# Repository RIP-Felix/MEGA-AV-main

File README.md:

# MegaAV
Sega Genesis audio and video bypass, incorporating an entirely new audio circuit design that restores mono audio, along with native composite and S-video generation.

Attribution: Credit where Credit's due

Timeline of events:
ACE9921 & Villahed94 developed the original Mega Amp 1.0. Inception for a mod board that combines the Mega Amp with an RGB video amplifier was Bob from RetroRGB's idea. Rene from db Electronics designed the first build. Tienfeng designed the second with a modified version of the then new Mega Amp 2.0, on which Jose Cruz helped with testing. That became the Triple Bypass v2.

Zaxour forked the 3BPv2 to support Composite restore with the 3BPV2+ and is continuing development of a Quadruple Bypass that will support S-video.

For most of the 6 years between the Mega Amp 2.0 and 3.0, Ace was pretty much developing alone. Villahed94, eep386, and ACE9921 were throwing ideas around, but nobody except Ace was doing anything. I want to make it clear that the Mega Amp 3 is it's own standalone thing still in development and that the Mega Audio is NOT to be confused with it. Ace is not associated with the MegaAV.

While they may use similar circuit topology, their goals are different, and they must not be used interchangeably

RIP-Felix incepted the idea of restoring Mono Audio for RF compatibility. RGBeter incepted the idea of recreating Composite video using a modern encoder, taking the opportunity to fix the luma trap. At that point it was still a derivative work of the 3BPV2+. Villahed94 agreed to join the MegaAV team to finish and implement the Mega Audio for both inboard and MegaAV mod board installations. The three of us tested and refined finalized values, and implemented the designs together. Both RIP-Felix and RGBeter designed the MegaAV PCB. The only part of the circuit that has remained unchanged is the THS7374 RGB amplifier. 

So the Mega AV is actually 2 mods in one. The Mega Video developed by RIP-Felix, RGBeter, and Villahed94. Mega Audio was developed with help from Villahed94 and others along the way. Villahed94, RGBeter and RIP-Felix dialed in PSG and FM resistor values to dial in MD fourier. That said I (RIP-Felix) want to thank and credit everyone involved in these mods regardless of how much of their contributions made it into the current version of Mega AV. It's been a collective effort and everyone should be credited for the hard work they've put in! Massive thanks to all of you!
 
NOTEs:
- Fujitsu ASICs, 315-5708-01 and 315-5660-01 needed an additional pulldown resistor. Instead of bridging jumper C, solder a 200Ohm 1% or lower tolerance resistor to it. May apply to Model 1 VA7 through Model 2 VA1.8. The Suffix -01 indicates it's a Fujitsu Chip. This DOES NOT apply to chips LACKING the suffix "-01".
- Adds a ZIF connector for a future ribbon cable design to greatly simplify installation

(instructions pending, same as 3bp install except composite and mono must also be isolated from the din, and the subcarrier line must be routed to the MegaAV)
### When routing the subcarrier line, make sure it's a shielded coaxial cable or twisted pair to prevent jailbars

Instructions pending:
## Model 1 Installation Guides
[Model 1 - VA1-VA6]
[Model 1 - VA7]
## Model 2 Installation Guides
[Model 2 - VA0-1.8]
[Model 2 - VA2]
[Model 2 - VA2.3] (needed)
[Model 2 - VA3]
[Model 2 - VA4]

## Model 3 Installation Guides
[Model 3 - VA1] (needed)
[Model 3 - VA2] (needed)

## Sega CDX
[CDX]

## Other
[Other forms of Genesis]

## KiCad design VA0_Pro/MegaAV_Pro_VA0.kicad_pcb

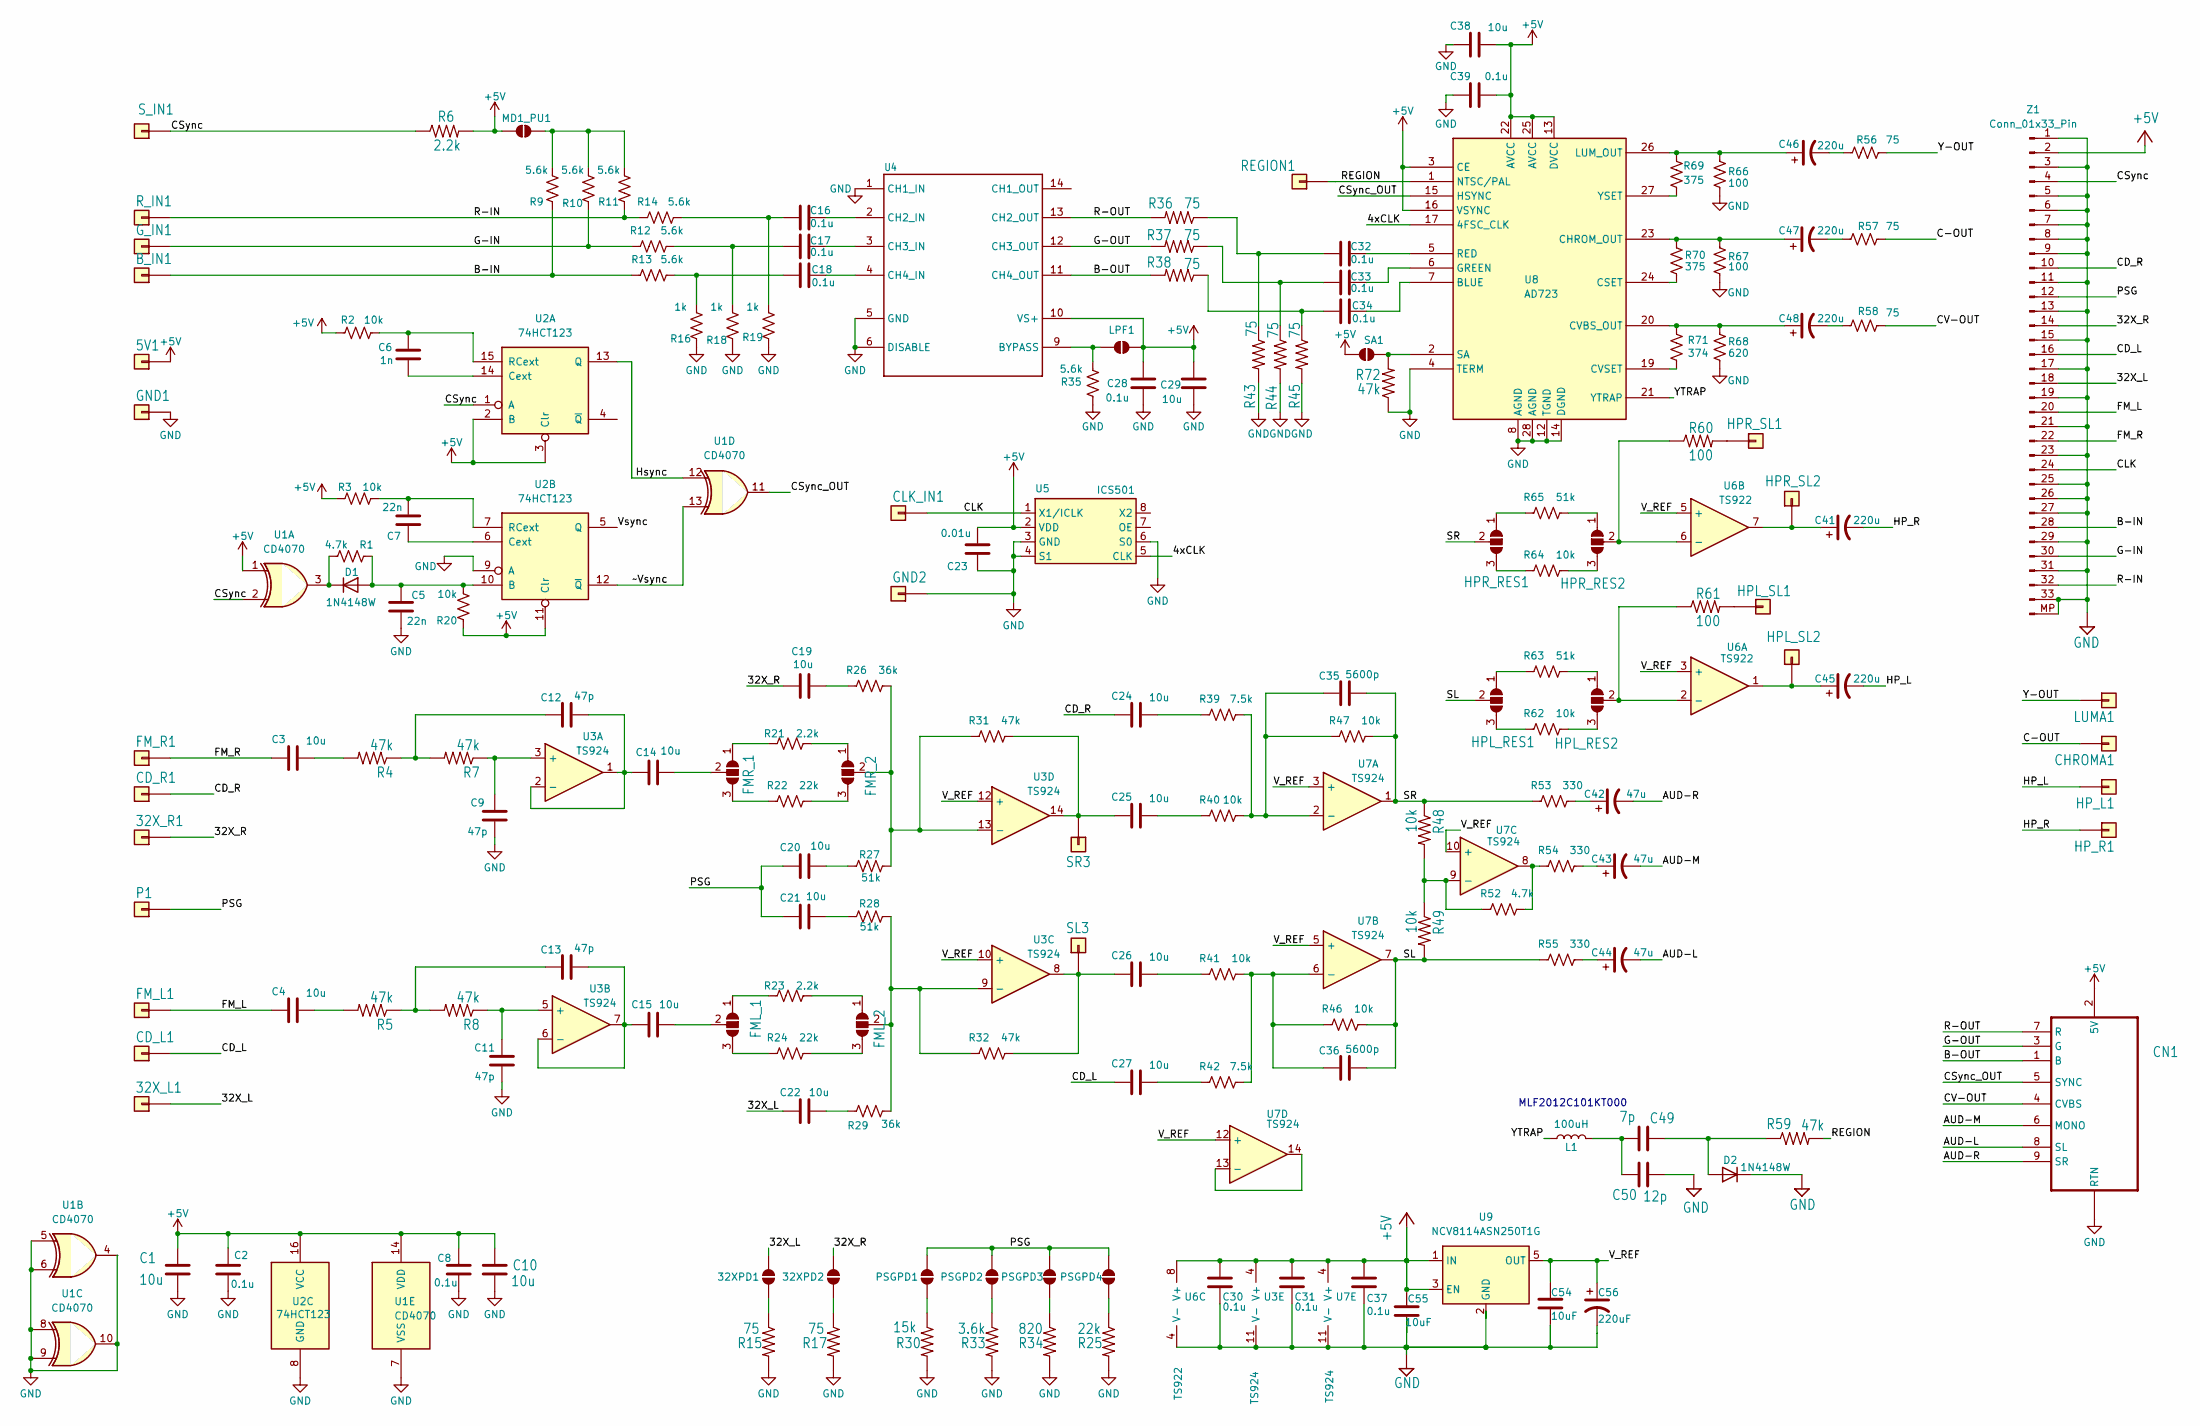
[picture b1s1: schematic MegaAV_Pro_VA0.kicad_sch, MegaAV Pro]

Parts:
5V1: SolderWirePad_1x01_SMD_1x2mm
32XPD1, 32XPD2: SolderJumper-2_P1.3mm_Open_RoundedPad1.0x1.5mm
32X_L1, 32X_R1: SMD_Conn_01x01; SolderWirePad_1x01_SMD_1x2mm
B_IN1: SolderWirePad_1x01_SMD_1x2mm
C1, C3, C4, C10, C14, C15, C19, C20, C21, C22, C24, C25, C26, C27, C29, C38: 10u; C_0805_2012Metric
C2, C8, C16, C17, C18, C30, C31, C32, C33, C34, C37, C39: 0.1u; C_0402_1005Metric
C5, C7: 22n; C_0402_1005Metric
C6: 1n; C_0402_1005Metric
C9, C11, C12, C13: 47p; C_0402_1005Metric
C23: 0.01u; C_0402_1005Metric
C28: 0.1u; C_0805_2012Metric
C35, C36: 5600p; C_0402_1005Metric
C41, C45, C46, C47, C48: 220u; CP_EIA-3528-15_AVX-H
C42, C43, C44: 47u; C_1206_3216Metric
C49: 7p; C_0402_1005Metric
C50: 12p; C_0402_1005Metric
C54: 10uF; C_0805_2012Metric; MPN VJ0805A330FXJPW1BC; LCSC Part # C520060
C55: 10uF; C_0805_2012Metric
C56: 220uF; CP_EIA-3528-15_AVX-H
CD_L1: SMD_Conn_01x01; SolderWirePad_1x01_SMD_1x2mm
CD_R1: SMD_Conn_01x01; SolderWirePad_1x01_SMD_1x2mm
CHROMA1: SMD_Conn_01x01; SolderWirePad_1x01_SMD_1x2mm
CLK_IN1: SolderWirePad_1x01_SMD_1x2mm
CN1: MD-90SM_MD2; MD90SM-MD2
D1, D2: 1N4148W; D_SOD-323F
FML_1, FML_2: SolderJumper_3_Open; SolderJumper-3_P1.3mm_Open_RoundedPad1.0x1.5mm
FMR_1, FMR_2: SolderJumper_3_Open; SolderJumper-3_P1.3mm_Open_RoundedPad1.0x1.5mm
FM_L1: SMD_Conn_01x01; SolderWirePad_1x01_SMD_1x2mm
FM_R1: SMD_Conn_01x01; SolderWirePad_1x01_SMD_1x2mm
GND1: SolderWirePad_1x01_SMD_1x2mm
GND2: SMD_Conn_01x01; SolderWirePad_1x01_SMD_1x2mm
G_IN1: SolderWirePad_1x01_SMD_1x2mm
HPL_RES1, HPL_RES2: SolderJumper_3_Open; SolderJumper-3_P1.3mm_Open_RoundedPad1.0x1.5mm
HPL_SL1, HPL_SL2: SMD_Conn_01x01; SolderWirePad_1x01_SMD_1x2mm
HPR_RES1, HPR_RES2: SolderJumper_3_Open; SolderJumper-3_P1.3mm_Open_RoundedPad1.0x1.5mm
HPR_SL1, HPR_SL2: SMD_Conn_01x01; SolderWirePad_1x01_SMD_1x2mm
HP_L1: SMD_Conn_01x01; SolderWirePad_1x01_SMD_1x2mm
HP_R1: SMD_Conn_01x01; SolderWirePad_1x01_SMD_1x2mm
L1: 100uH; L_0805_2012Metric
LPF1: SolderJumper-2_P1.3mm_Open_RoundedPad1.0x1.5mm
LUMA1: SMD_Conn_01x01; SolderWirePad_1x01_SMD_1x2mm
MD1_PU1: SolderJumper-2_P1.3mm_Open_RoundedPad1.0x1.5mm
P1: SMD_Conn_01x01; SolderWirePad_1x01_SMD_1x2mm
PSGPD1, PSGPD2, PSGPD3, PSGPD4: SolderJumper-2_P1.3mm_Open_RoundedPad1.0x1.5mm
R1, R52: 4.7k; R_0402_1005Metric
R2, R3, R20, R40, R41, R46, R47, R48, R49, R62, R64: 10k; R_0402_1005Metric
R4, R5, R7, R8, R31, R32, R59, R72: 47k; R_0402_1005Metric
R6, R21, R23: 2.2k; R_0402_1005Metric
R9, R10, R11, R12, R13, R14, R35: 5.6k; R_0603_1608Metric
R15, R17, R36, R37, R38, R43, R44, R45, R56, R57, R58: 75; R_0603_1608Metric
R16, R18, R19: 1k; R_0402_1005Metric
R22, R24, R25: 22k; R_0402_1005Metric
R26, R29: 36k; R_0603_1608Metric
R27, R28, R63, R65: 51k; R_0402_1005Metric
R30: 15k; R_0402_1005Metric
R33: 3.6k; R_0603_1608Metric
R34: 820; R_0603_1608Metric
R39, R42: 7.5k; R_0603_1608Metric
R53, R54, R55: 330; R_0402_1005Metric
R60, R61, R66, R67: 100; R_0402_1005Metric
R68: 620; R_0402_1005Metric
R69, R70: 375; R_0402_1005Metric
R71: 374; R_0402_1005Metric
REGION1: SolderWirePad_1x01_SMD_1x2mm
R_IN1: SolderWirePad_1x01_SMD_1x2mm
SA1: SolderJumper-2_P1.3mm_Open_RoundedPad1.0x1.5mm
SL3: SMD_Conn_01x01; SolderWirePad_1x01_SMD_1x2mm
SR3: SMD_Conn_01x01; SolderWirePad_1x01_SMD_1x2mm
S_IN1: SolderWirePad_1x01_SMD_1x2mm
U1: CD4070; TSSOP-14_4.4x5mm_P0.65mm
U2: 74HCT123; TSSOP-16_4.4x5mm_P0.65mm
U3, U7: TS924; TSSOP-14_4.4x5mm_P0.65mm
U4: THS7374; TSSOP-14_4.4x5mm_P0.65mm
U5: ICS501; SOIC-8_3.9x4.9mm_P1.27mm
U6: TS922; SO-8_3.9x4.9mm_P1.27mm
U8: AD723; TSSOP-28_6.1x9.7mm_P0.65mm
U9: NCV8114ASN250T1G; TSOT-23-5
Z1: Conn_01x33_Pin; Molex_502244-3330_1x33-1MP_P0.5mm_Horizontal

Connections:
+5V: 5V1.1, C1.1, C2.1, C8.1, C10.1, C23.2, C28.1, C29.1, C30.1, C31.1, C37.1, C38.2, C39.2, C55.1, CN1.2 (5V), LPF1.2 (B), MD1_PU1.2 (B), R2.2, R3.1, R6.2, R20.1, SA1.1 (A), U1.1, U1.14 (VDD), U2.2 (B), U2.3 (Clr), U2.11 (Clr), U2.16 (VCC), U3.4 (V+), U4.10 (VS+), U5.2 (VDD), U6.8 (V+), U7.4 (V+), U8.3 (CE), U8.13 (DVCC), U8.16 (VSYNC), U8.22 (AVCC), U8.25 (AVCC), U9.1 (IN), U9.3 (EN), Z1.2
/4xCLK: U5.5 (CLK), U8.17 (4FSC_CLK)
/32X_L: 32XPD1.2 (B), 32X_L1.1, C22.1, Z1.18
/32X_R: 32XPD2.2 (B), 32X_R1.1, C19.1, Z1.14
/AUD-L: C44.2, CN1.8 (SL)
/AUD-M: C43.2, CN1.6 (MONO)
/AUD-R: C42.2, CN1.9 (SR)
/B-IN: B_IN1.1, R9.1, R13.1, Z1.28
/B-OUT: CN1.1 (B), R38.2, U4.11 (CH4_OUT)
/C-OUT: CHROMA1.1, R57.2
/CD_L: C27.1, CD_L1.1, Z1.16
/CD_R: C24.1, CD_R1.1, Z1.10
/CLK: CLK_IN1.1, U5.1 (X1/ICLK), Z1.24
/CSync: R6.1, S_IN1.1, U1.2, U2.1 (A), Z1.4
/CSync_OUT: CN1.5 (SYNC), U1.11, U8.15 (HSYNC)
/CV-OUT: CN1.4 (CVBS), R58.2
/FM_L: C4.1, FM_L1.1, Z1.20
/FM_R: C3.1, FM_R1.1, Z1.22
/G-IN: G_IN1.1, R10.1, R12.1, Z1.30
/G-OUT: CN1.3 (G), R37.2, U4.12 (CH3_OUT)
/HP_L: C45.2, HP_L1.1
/HP_R: C41.2, HP_R1.1
/Hsync: U1.12, U2.13 (Q)
/PSG: C20.1, C21.1, P1.1, PSGPD1.2 (B), PSGPD2.2 (B), PSGPD3.2 (B), PSGPD4.2 (B), Z1.12
/R-IN: R11.1, R14.1, R_IN1.1, Z1.32
/R-OUT: CN1.7 (R), R36.2, U4.13 (CH2_OUT)
/REGION: R59.2, REGION1.1, U8.1 (NTSC/PAL); also elsewhere on the board
/SL: C36.2, HPL_RES1.2 (C), R46.2, R49.2, R55.1, U7.7
/SR: C35.2, HPR_RES1.2 (C), R47.2, R48.1, R53.1, U7.1
/V_REF: C54.1, C56.1, U3.10 (+), U3.12 (+), U6.3 (+), U6.5 (+), U7.3 (+), U7.5 (+), U7.10 (+), U7.12 (+), U9.5 (OUT)
/Vsync: U2.5 (Q)
/Y-OUT: LUMA1.1, R56.2
/YTRAP: L1.1, U8.21 (YTRAP)
/~Vsync: U1.13, U2.12 (~Q)
GND: C1.2, C2.2, C5.1, C8.2, C9.2, C10.2, C11.2, C23.1, C28.2, C29.2, C30.2, C31.2, C37.2, C38.1, C39.1, C50.2, C54.2, C55.2, C56.2, CN1.S1 (RTN), CN1.S2 (RTN), CN1.S3 (RTN), D2.1 (K), GND1.1, GND2.1, R15.2, R16.1, R17.2, R18.1, R19.1, R25.2, R30.2, R33.2, R34.2, R35.1, R43.2, R44.2, R45.2, R66.2, R67.2, R68.2, R72.1, U1.4, U1.5, U1.6, U1.7 (VSS), U1.8, U1.9, U1.10, U2.8 (GND), U2.9 (A), U3.11 (V-), U4.1 (CH1_IN), U4.5 (GND), U4.6 (DISABLE), U5.3 (GND), U5.4 (S1), U5.6 (S0), U6.4 (V-), U7.11 (V-), U8.4 (TERM), U8.8 (AGND), U8.12 (TGND), U8.14 (DGND), U8.28 (AGND), U9.2 (GND), Z1.1, Z1.3, Z1.5, Z1.6, Z1.7, Z1.8, Z1.9, Z1.11, Z1.13, Z1.15, Z1.17, Z1.19, Z1.21, Z1.23, Z1.25, Z1.26, Z1.27, Z1.29, Z1.31, Z1.33, Z1.MP
unnamed: 32XPD1.1 (A), R15.1
unnamed: 32XPD2.1 (A), R17.1
unnamed: C3.2, R4.2
unnamed: C4.2, R5.2
unnamed: C12.1, R4.1, R7.2
unnamed: C13.1, R5.1, R8.2
unnamed: C16.1, R14.2, R19.2
unnamed: C17.1, R12.2, R18.2
unnamed: C18.1, R13.2, R16.2
unnamed: C19.2, R26.1
unnamed: C20.2, R27.1
unnamed: C21.2, R28.1
unnamed: C22.2, R29.1
unnamed: C24.2, R39.1
unnamed: C25.2, R40.1
unnamed: C26.2, R41.1
unnamed: C27.2, R42.1
unnamed: C32.1, R36.1, R43.1
unnamed: C33.1, R37.1, R44.1
unnamed: C34.1, R38.1, R45.1
unnamed: C42.1, R53.2
unnamed: C43.1, R54.2
unnamed: C44.1, R55.2
unnamed: C46.2, R56.1
unnamed: C47.2, R57.1
unnamed: C48.2, R58.1
unnamed: C49.2, C50.1, L1.2
unnamed: C5.2, D1.2 (A), R1.1, R20.2, U2.10 (B)
unnamed: D1.1 (K), R1.2, U1.3
unnamed: C49.1, D2.2 (A), R59.1
unnamed: FML_1.1 (A), R23.1
unnamed: FML_1.3 (B), R24.1
unnamed: C15.2, FML_1.2 (C)
unnamed: FML_2.1 (A), R23.2
unnamed: FML_2.3 (B), R24.2
unnamed: FML_2.2 (C), R28.2, R29.2, R32.1, U3.9 (-)
unnamed: FMR_1.1 (A), R21.1
unnamed: FMR_1.3 (B), R22.1
unnamed: C14.2, FMR_1.2 (C)
unnamed: FMR_2.1 (A), R21.2
unnamed: FMR_2.3 (B), R22.2
unnamed: FMR_2.2 (C), R26.2, R27.2, R31.1, U3.13 (-)
unnamed: HPL_RES1.1 (A), R63.1
unnamed: HPL_RES1.3 (B), R62.1
unnamed: HPL_RES2.1 (A), R63.2
unnamed: HPL_RES2.3 (B), R62.2
unnamed: HPL_RES2.2 (C), R61.1, U6.2 (-)
unnamed: HPL_SL1.1, R61.2
unnamed: C45.1, HPL_SL2.1, U6.1
unnamed: HPR_RES1.1 (A), R65.1
unnamed: HPR_RES1.3 (B), R64.1
unnamed: HPR_RES2.1 (A), R65.2
unnamed: HPR_RES2.3 (B), R64.2
unnamed: HPR_RES2.2 (C), R60.1, U6.6 (-)
unnamed: HPR_SL1.1, R60.2
unnamed: C41.1, HPR_SL2.1, U6.7
unnamed: LPF1.1 (A), R35.2, U4.9 (BYPASS)
unnamed: MD1_PU1.1 (A), R9.2, R10.2, R11.2
unnamed: PSGPD1.1 (A), R30.1
unnamed: PSGPD2.1 (A), R33.1
unnamed: PSGPD3.1 (A), R34.1
unnamed: PSGPD4.1 (A), R25.1
unnamed: R52.2, R54.1, U7.8
unnamed: R72.2, SA1.2 (B), U8.2 (SA)
unnamed: C26.1, R32.2, SL3.1, U3.8
unnamed: C25.1, R31.2, SR3.1, U3.14
unnamed: C6.1, U2.14 (Cext)
unnamed: C6.2, R2.1, U2.15 (RCext)
unnamed: C7.1, U2.6 (Cext)
unnamed: C7.2, R3.2, U2.7 (RCext)
unnamed: C9.1, R7.1, U3.3 (+)
unnamed: C12.2, C14.1, U3.1, U3.2 (-)
unnamed: C11.1, R8.1, U3.5 (+)
unnamed: C13.2, C15.1, U3.6 (-), U3.7
unnamed: C16.2, U4.2 (CH2_IN)
unnamed: C17.2, U4.3 (CH3_IN)
unnamed: C18.2, U4.4 (CH4_IN)
unnamed: C35.1, R39.2, R40.2, R47.1, U7.2 (-)
unnamed: C36.1, R41.2, R42.2, R46.1, U7.6 (-)
unnamed: R48.2, R49.1, R52.1, U7.9 (-)
unnamed: U7.13 (-), U7.14
unnamed: C34.2, U8.7 (BLUE)
unnamed: C47.1, R67.1, R70.2, U8.23 (CHROM_OUT)
unnamed: R70.1, U8.24 (CSET)
unnamed: C48.1, R68.1, R71.2, U8.20 (CVBS_OUT)
unnamed: R71.1, U8.19 (CVSET)
unnamed: C33.2, U8.6 (GREEN)
unnamed: C46.1, R66.1, R69.1, U8.26 (LUM_OUT)
unnamed: C32.2, U8.5 (RED)
unnamed: R69.2, U8.27 (YSET)

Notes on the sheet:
MLF2012C101KT000

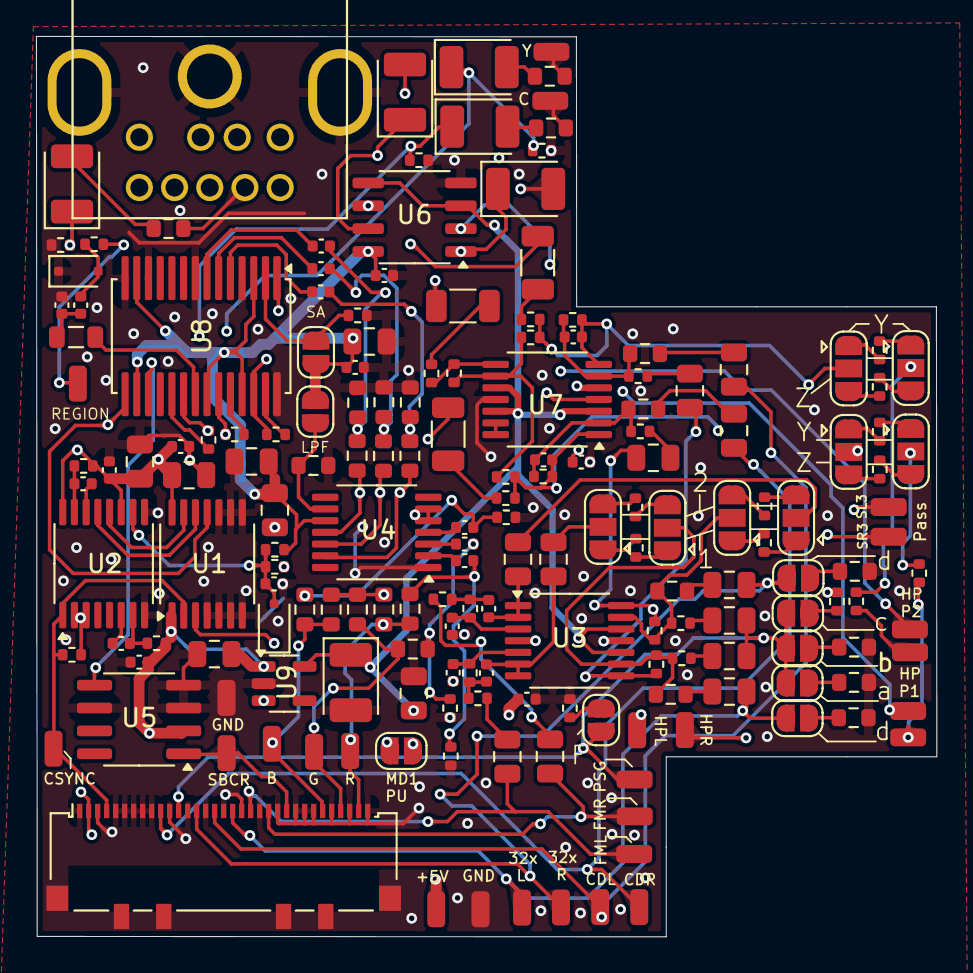
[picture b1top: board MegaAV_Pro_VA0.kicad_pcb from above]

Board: 4 copper layers, 50.0 x 50.0 mm, 179 parts (0 on the bottom side), 124 nets.

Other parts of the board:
REGION: SolderWirePad_1x01_SMD_1x2mm

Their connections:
/REGION: REGION.1; also elsewhere on the board

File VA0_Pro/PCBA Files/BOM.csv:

Designator,Comment,Footprint,LCSC Part #
"R15,R17,R36,R37,R38,R43,R44,R45,R56,R57,R58",75,Resistor_SMD:R_0603_1608Metric,C4275
"R60,R61,R66,R67",100,Resistor_SMD:R_0402_1005Metric,C25076
"R53,R54,R55",330,Resistor_SMD:R_0402_1005Metric,C25104
"R69,R70,R71",374,Resistor_SMD:R_0402_1005Metric,C270604
R68,620,Resistor_SMD:R_0402_1005Metric,C4961
R34,820,Resistor_SMD:R_0603_1608Metric,C23253
C23,0.01u,Capacitor_SMD:C_0402_1005Metric,C15195
"C2,C8,C28,C30,C31,C32,C33,C34,C37,C39",100n,Capacitor_SMD:C_0402_1005Metric,C28233
"C16,C17,C18",0.1u,Capacitor_SMD:C_0402_1005Metric,C1525
L1,100uH,Inductor_SMD:L_0805_2012Metric,C68035
"R2,R3,R20,R40,R41,R46,R47,R48,R49,R62,R64",10k,Resistor_SMD:R_0402_1005Metric,C25744
"C1,C3,C4,C10,C14,C15,C19,C20,C21,C22,C24,C25,C26,C27,C29,C38,C54,C55",10u,Capacitor_SMD:C_0805_2012Metric,C15850
C50,12p,Capacitor_SMD:C_0402_1005Metric,C1547
R30,15k,Resistor_SMD:R_0402_1005Metric,C25756
"R16,R18,R19",1k,Resistor_SMD:R_0402_1005Metric,C11702
C6,1n,Capacitor_SMD:C_0402_1005Metric,C1523
"D1,D2",1N4148W,Diode_SMD:D_SOD-323,C2128
"R6,R21,R23",2.2k,Resistor_SMD:R_0402_1005Metric,C25879
"C41,C45,C46,C47,C48,C56",220u,Capacitor_Tantalum_SMD:CP_EIA-3528-15_AVX-H,C122649
"R22,R24,R25",22k,Resistor_SMD:R_0402_1005Metric,C25768
"C5,C7",22n,Capacitor_SMD:C_0402_1005Metric,C1532
R33,3.6k,Resistor_SMD:R_0603_1608Metric,C22980
"R26,R29",36k,Resistor_SMD:R_0603_1608Metric,C23147
"R1,R52",4.7k,Resistor_SMD:R_0402_1005Metric,C25900
"R4,R5,R7,R8,R31,R32,R59,R72",47k,Resistor_SMD:R_0402_1005Metric,C25792
"C9,C11,C12,C13",47p,Capacitor_SMD:C_0402_1005Metric,C1567
"C42,C43,C44",47u,Capacitor_SMD:C_1206_3216Metric,C96123
"R9,R10,R11,R12,R13,R14,R35",5.6k,Resistor_SMD:R_0603_1608Metric,C23189
"R27,R28,R63,R65",51k,Resistor_SMD:R_0402_1005Metric,C25794
"C35,C36",5600p,Capacitor_SMD:C_0402_1005Metric,C2976066
"R39,R42",7.5k,Resistor_SMD:R_0603_1608Metric,C23234
U2,74HCT123,Package_SO:TSSOP-16_4.4x5mm_P0.65mm,C191980
C49,7p,Capacitor_SMD:C_0402_1005Metric,C5448838
U8,AD723,Package_SO:TSSOP-28_6.1x9.7mm_P0.65mm,
U1,CD4070,Package_SO:TSSOP-14_4.4x5mm_P0.65mm,C2865674
Z1,Conn_01x33_Pin,Connector_FFC-FPC:Molex_502244-3330_1x33-1MP_P0.5mm_Horizontal,
U5,ICS501,Package_SO:SOIC-8_3.9x4.9mm_P1.27mm,
CN1,MD-90SM_MD2,MyLibrary:MD90SM-MD2,
U9,2.5v linear Regulator,Package_TO_SOT_SMD:TSOT-23-5,C22466441
U4,THS7374,Package_SO:TSSOP-14_4.4x5mm_P0.65mm,
U6,TS922,Package_SO:TSSOP-8_4.4x3mm_P0.65mm,C93687
"U3,U7",TS924,Package_SO:TSSOP-14_4.4x5mm_P0.65mm,

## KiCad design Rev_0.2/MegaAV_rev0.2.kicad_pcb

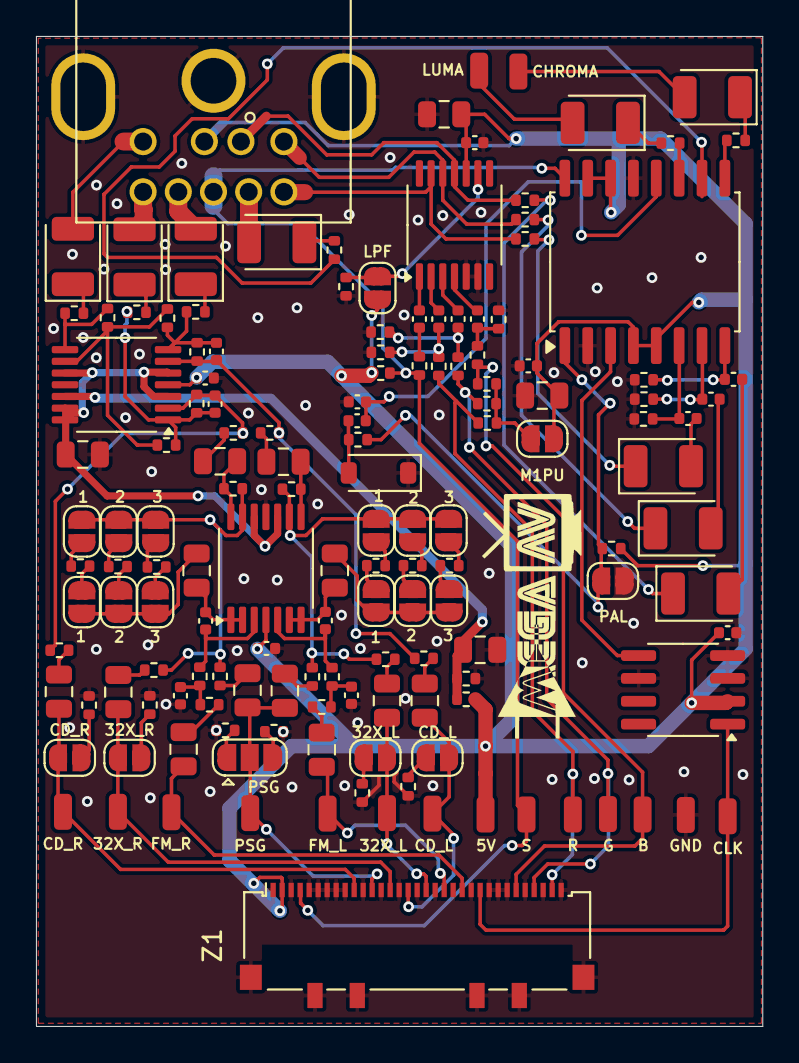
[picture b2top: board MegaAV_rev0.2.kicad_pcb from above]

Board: 2 copper layers, 40.4 x 55.0 mm, 148 parts (0 on the bottom side), 103 nets.

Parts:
5V: SolderWirePad_1x01_SMD_1x2mm
32X_L, 32X_R: SMD_Conn_01x01; SolderWirePad_1x01_SMD_1x2mm
32X_L#2, 32X_R#2: SolderJumper-2_P1.3mm_Open_RoundedPad1.0x1.5mm
B: SolderWirePad_1x01_SMD_1x2mm
C1: 0.01u; C_0402_1005Metric
C2, C3, C8, C9, C14, C15, C16, C17, C19, C20, C21, C22, C23, C32, C42, C45: 10u; C_0805_2012Metric
C4, C5, C6, C7: 27p; C_0402_1005Metric
C10, C11, C12, C13, C18, C27, C28, C29, C33, C43, C44: 0.1u; C_0402_1005Metric
C24, C25, C26, C39, C40, C41: 220u; CP_EIA-3528-15_AVX-H
C30, C31: 5600p; C_0402_1005Metric
C34, C35, C36: 47u; CP_EIA-3528-15_AVX-H
C37: 9p; C_0402_1005Metric
C38: 18p; C_0402_1005Metric
CD_L: SMD_Conn_01x01; SolderWirePad_1x01_SMD_1x2mm
CD_L#2: SolderJumper-2_P1.3mm_Open_RoundedPad1.0x1.5mm
CD_R: SolderJumper-2_P1.3mm_Open_RoundedPad1.0x1.5mm
CD_R#2: SMD_Conn_01x01; SolderWirePad_1x01_SMD_1x2mm
CHROMA: SMD_Conn_01x01; SolderWirePad_1x01_SMD_1x2mm
CLK: SolderWirePad_1x01_SMD_1x2mm
CN1: MD-90SM_MD2; MD90SM-MD2
D1: 1N4148W; D_SOD-123
FM_L: SMD_Conn_01x01; SolderWirePad_1x01_SMD_1x2mm
FM_L1-1, FM_L1-2, FM_L2-1, FM_L2-2, FM_L3-1, FM_L3-2: SolderJumper_2_Open; SolderJumper-2_P1.3mm_Open_RoundedPad1.0x1.5mm
FM_R: SMD_Conn_01x01; SolderWirePad_1x01_SMD_1x2mm
FM_R1-1, FM_R1-2, FM_R2-1, FM_R2-2, FM_R3-1, FM_R3-2: SolderJumper_2_Open; SolderJumper-2_P1.3mm_Open_RoundedPad1.0x1.5mm
G: SolderWirePad_1x01_SMD_1x2mm
GND: SolderWirePad_1x01_SMD_1x2mm
LPF: SolderJumper-2_P1.3mm_Open_RoundedPad1.0x1.5mm
LUMA: SMD_Conn_01x01; SolderWirePad_1x01_SMD_1x2mm
M1PU: SolderJumper-2_P1.3mm_Open_RoundedPad1.0x1.5mm
PAL: SolderJumper-2_P1.3mm_Open_RoundedPad1.0x1.5mm
PSG: SMD_Conn_01x01; SolderWirePad_1x01_SMD_1x2mm
PSG#2: SolderJumper_3_Open; SolderJumper-3_P1.3mm_Open_RoundedPad1.0x1.5mm
R: SolderWirePad_1x01_SMD_1x2mm
R1, R2, R3, R4, R20, R23, R48, R49: 100k; R_0402_1005Metric
R5, R8: 2.2k; R_0402_1005Metric
R6, R9, R10, R11, R12, R13, R16, R32, R42: 5.62k; R_0402_1005Metric
R7: 750; R_0402_1005Metric
R14, R15, R17: 1k; R_0402_1005Metric
R18, R25, R33, R34, R35, R36, R37, R43, R44, R46, R54, R55, R56: 75; R_0402_1005Metric
R19, R22, R58, R59: 10k; R_0402_1005Metric
R21, R24: 130k; R_0402_1005Metric
R26, R27, R28, R29: 210k; R_0402_1005Metric
R30, R31: 300k; R_0402_1005Metric
R38, R41: 21k; R_0402_1005Metric
R39, R40, R45, R47: 30k; R_0402_1005Metric
R50, R51, R53: 330; R_0402_1005Metric
R52: 51k; R_0402_1005Metric
R57: 470; R_0402_1005Metric
S: SolderWirePad_1x01_SMD_1x2mm
U1: ICS501; SOIC-8_3.9x4.9mm_P1.27mm
U2, U4: MC33204; TSSOP-14_4.4x5mm_P0.65mm
U3: THS7374; TSSOP-14_4.4x5mm_P0.65mm
U5: AD725; SOIC-16W_7.5x10.3mm_P1.27mm
Z1: Conn_01x33_Pin; Molex_502244-3330_1x33-1MP_P0.5mm_Horizontal

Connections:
+5V: 5V.1, C1.2, C18.1, C23.1, C32.2, C33.2, C43.1, C44.1, CN1.2 (5V), LPF.2 (B), M1PU.2 (B), R5.2, R42.1, R58.2, U1.2 (VDD), U2.4 (V+), U3.10 (VS+), U4.4 (V+), U5.4 (AVCC), U5.5 (CE), U5.14 (DVCC), U5.15 (VSYNC), Z1.2
/2V5: C45.1, R58.1, R59.2, U4.12 (+)
/4xCLK: U1.5 (CLK), U5.3 (4FSC_CLK)
/32X_L: 32X_L.1, 32X_L#2.2 (B), C17.1, Z1.18
/32X_R: 32X_R.1, 32X_R#2.1 (A), C14.1, Z1.14
/AUD-L: C35.2, CN1.8 (SL)
/AUD-M: C36.2, CN1.6 (MONO)
/AUD-R: C34.2, CN1.9 (SR)
/B-IN: B.1, R6.1, R13.1, Z1.28
/B-OUT: CN1.1 (B), R36.1, U3.11 (CH4_OUT)
/C-OUT: C40.2, CHROMA.1
/CD_L: C22.1, CD_L.1, CD_L#2.2 (B), Z1.16
/CD_R: C19.1, CD_R.2 (B), CD_R#2.1, Z1.10
/CLK: CLK.1, U1.1 (X1/ICLK), Z1.24
/CSync: CN1.5 (SYNC), R5.1, R16.1, S.1, U5.16 (HSYNC), Z1.4
/CV-OUT: C41.2, CN1.4 (CVBS)
/FM_L: C3.1, FM_L.1, Z1.20
/FM_R: C2.1, FM_R.1, Z1.22
/G-IN: G.1, R9.1, R12.1, Z1.30
/G-OUT: CN1.3 (G), R35.1, U3.12 (CH3_OUT)
/PSG: C15.1, C16.1, PSG.1, PSG#2.2 (C), Z1.12
/R-IN: R.1, R10.1, R11.1, Z1.32
/R-OUT: CN1.7 (R), R34.1, U3.13 (CH2_OUT)
/STDSEL: PAL.1 (A), R42.2, R57.2, U5.1 (NTSC/PAL)
/V_REF: C42.1, U2.10 (+), U2.12 (+), U4.3 (+), U4.5 (+), U4.10 (+), U4.13 (-), U4.14
/Y-OUT: C39.2, LUMA.1
GND: C1.1, C4.2, C5.2, C18.2, C23.2, C32.1, C33.1, C38.2, C42.2, C43.2, C44.2, C45.2, CN1.S1 (RTN), CN1.S2 (RTN), CN1.S3 (RTN), D1.1 (K), GND.1, PAL.2 (B), R7.2, R8.2, R14.1, R15.1, R17.1, R18.2, R25.1, R32.1, R33.2, R37.2, R43.1, R44.1, R46.1, R59.1, U1.3 (GND), U1.4 (S1), U1.6 (S0), U2.11 (V-), U3.5 (GND), U3.6 (DISABLE), U4.11 (V-), U5.2 (AGND), U5.13 (DGND), Z1.1, Z1.3, Z1.5, Z1.6, Z1.7, Z1.8, Z1.9, Z1.11, Z1.13, Z1.15, Z1.17, Z1.19, Z1.21, Z1.23, Z1.25, Z1.26, Z1.27, Z1.29, Z1.31, Z1.33, Z1.MP
unnamed: 32X_L#2.1 (A), R18.1
unnamed: 32X_R#2.2 (B), R25.2
unnamed: C2.2, R1.2
unnamed: C3.2, R2.2
unnamed: C4.1, R1.1, R3.2
unnamed: C5.1, R2.1, R4.2
unnamed: C10.1, R16.2
unnamed: C11.1, R11.2, R17.2
unnamed: C12.1, R12.2, R15.2
unnamed: C13.1, R13.2, R14.2
unnamed: C14.2, R26.1
unnamed: C15.2, R27.1
unnamed: C16.2, R28.1
unnamed: C17.2, R29.1
unnamed: C19.2, R38.1
unnamed: C20.1, R30.2, U2.14
unnamed: C20.2, R39.1
unnamed: C21.1, R31.2, U2.8
unnamed: C21.2, R40.1
unnamed: C22.2, R41.1
unnamed: C24.1, R34.2
unnamed: C24.2, C27.1
unnamed: C25.1, R35.2
unnamed: C25.2, C28.1
unnamed: C26.1, R36.2
unnamed: C26.2, C29.1
unnamed: C30.2, R47.2, R48.1, R50.1, U4.1
unnamed: C31.2, R45.2, R49.2, R51.1, U4.7
unnamed: C34.1, R50.2
unnamed: C35.1, R51.2
unnamed: C36.1, R53.2
unnamed: C39.1, R54.2
unnamed: C40.1, R55.2
unnamed: C41.1, R56.2
unnamed: CD_L#2.1 (A), R33.1
unnamed: CD_R.1 (A), R37.1
unnamed: C37.1, D1.2 (A), R57.1
unnamed: C9.2, FM_L1-1.1 (A), FM_L2-1.1 (A), FM_L3-1.1 (A)
unnamed: FM_L1-1.2 (B), R22.1
unnamed: FM_L1-2.1 (A), R22.2
unnamed: FM_L1-2.2 (B), FM_L2-2.2 (B), FM_L3-2.2 (B), R28.2, R29.2, R31.1, U2.9 (-)
unnamed: FM_L2-1.2 (B), R23.1
unnamed: FM_L2-2.1 (A), R23.2
unnamed: FM_L3-1.2 (B), R24.1
unnamed: FM_L3-2.1 (A), R24.2
unnamed: C8.2, FM_R1-1.1 (A), FM_R2-1.1 (A), FM_R3-1.1 (A)
unnamed: FM_R1-1.2 (B), R19.1
unnamed: FM_R1-2.1 (A), R19.2
unnamed: FM_R1-2.2 (B), FM_R2-2.2 (B), FM_R3-2.2 (B), R26.2, R27.2, R30.1, U2.13 (-)
unnamed: FM_R2-1.2 (B), R20.1
unnamed: FM_R2-2.1 (A), R20.2
unnamed: FM_R3-1.2 (B), R21.1
unnamed: FM_R3-2.1 (A), R21.2
unnamed: LPF.1 (A), R32.2, U3.9 (BYPASS)
unnamed: M1PU.1 (A), R6.2, R9.2, R10.2
unnamed: PSG#2.1 (A), R8.1
unnamed: PSG#2.3 (B), R7.1
unnamed: R52.2, R53.1, U4.8
unnamed: C6.1, R3.1, U2.3 (+)
unnamed: C6.2, C8.1, U2.1, U2.2 (-)
unnamed: C7.1, R4.1, U2.5 (+)
unnamed: C7.2, C9.1, U2.6 (-), U2.7
unnamed: C10.2, U3.1 (CH1_IN)
unnamed: C11.2, U3.2 (CH2_IN)
unnamed: C12.2, U3.3 (CH3_IN)
unnamed: C13.2, U3.4 (CH4_IN)
unnamed: C30.1, R38.2, R39.2, R47.1, U4.2 (-)
unnamed: C31.1, R40.2, R41.2, R45.1, U4.6 (-)
unnamed: R48.2, R49.1, R52.1, U4.9 (-)
unnamed: C29.2, R43.2, U5.8 (BLUE)
unnamed: R55.1, U5.9 (CHROM_OUT)
unnamed: R56.1, U5.10 (CVBS_OUT)
unnamed: C28.2, R44.2, U5.7 (GREEN)
unnamed: R54.1, U5.11 (LUM_OUT)
unnamed: C27.2, R46.2, U5.6 (RED)
unnamed: C37.2, C38.1, U5.12 (TRAP)

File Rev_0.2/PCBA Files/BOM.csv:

Comment,Designator,Footprint,JLCPCB Part #
0.01u,C1,Capacitor_SMD:C_0402_1005Metric,
10u,"C2,C3,C8,C9,C14,C15,C16,C17,C19,C20,C21,C22,C23,C32,C42,C45",Capacitor_SMD:C_0805_2012Metric,
27p,"C4,C5,C6,C7",Capacitor_SMD:C_0402_1005Metric,
0.1u,"C10,C11,C12,C13,C18,C27,C28,C29,C33,C43,C44",Capacitor_SMD:C_0402_1005Metric,
220u,"C24,C25,C26,C39,C40,C41",Capacitor_Tantalum_SMD:CP_EIA-3528-15_AVX-H,
5.6n,"C30,C31",Capacitor_SMD:C_0402_1005Metric,
47u,"C34,C35,C36",Capacitor_Tantalum_SMD:CP_EIA-3528-15_AVX-H,
9p,C37,Capacitor_SMD:C_0402_1005Metric,
18p,C38,Capacitor_SMD:C_0402_1005Metric,
1N4148W,D1,Diode_SMD:D_SOD-123,C81598
100k,"R1,R2,R3,R4,R20,R23,R48,R49",Resistor_SMD:R_0402_1005Metric,
2.2k,"R5,R8",Resistor_SMD:R_0402_1005Metric,
5.62k,"R6,R9,R10,R11,R12,R13,R16,R32,R42",Resistor_SMD:R_0402_1005Metric,
750,R7,Resistor_SMD:R_0402_1005Metric,
1k,"R14,R15,R17",Resistor_SMD:R_0402_1005Metric,
75,"R18,R25,R33,R34,R35,R36,R37,R43,R44,R46,R54,R55,R56",Resistor_SMD:R_0402_1005Metric,
10k,"R19,R22,R58,R59",Resistor_SMD:R_0402_1005Metric,
130k,"R21,R24",Resistor_SMD:R_0402_1005Metric,
210k,"R26,R27,R28,R29",Resistor_SMD:R_0402_1005Metric,
300k,"R30,R31",Resistor_SMD:R_0402_1005Metric,
21k,"R38,R41",Resistor_SMD:R_0402_1005Metric,
30k,"R39,R40,R45,R47",Resistor_SMD:R_0402_1005Metric,
330,"R50,R51,R53",Resistor_SMD:R_0402_1005Metric,
51k,R52,Resistor_SMD:R_0402_1005Metric,
470,R57,Resistor_SMD:R_0402_1005Metric,
ICS501,U1,Package_SO:SOIC-8_3.9x4.9mm_P1.27mm,
MC33204,"U2,U4",Package_SO:TSSOP-14_4.4x5mm_P0.65mm,
THS7374,U3,Package_SO:TSSOP-14_4.4x5mm_P0.65mm,
AD725,U5,Package_SO:SOIC-16W_7.5x10.3mm_P1.27mm,
Conn_01x33_Pin,Z1,Connector_FFC-FPC:Molex_502244-3330_1x33-1MP_P0.5mm_Horizontal,

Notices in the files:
Rev-/MiniDin9ZIF/4bp_ZIFF_MD9.kicad_pcb:
CERN OHL v1.2
Licensed under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
